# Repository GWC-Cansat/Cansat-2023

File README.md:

# Cansat-2023
The GWC Cansat 2023 files

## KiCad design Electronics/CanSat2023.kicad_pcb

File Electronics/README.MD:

The electronic files for cansat 2023

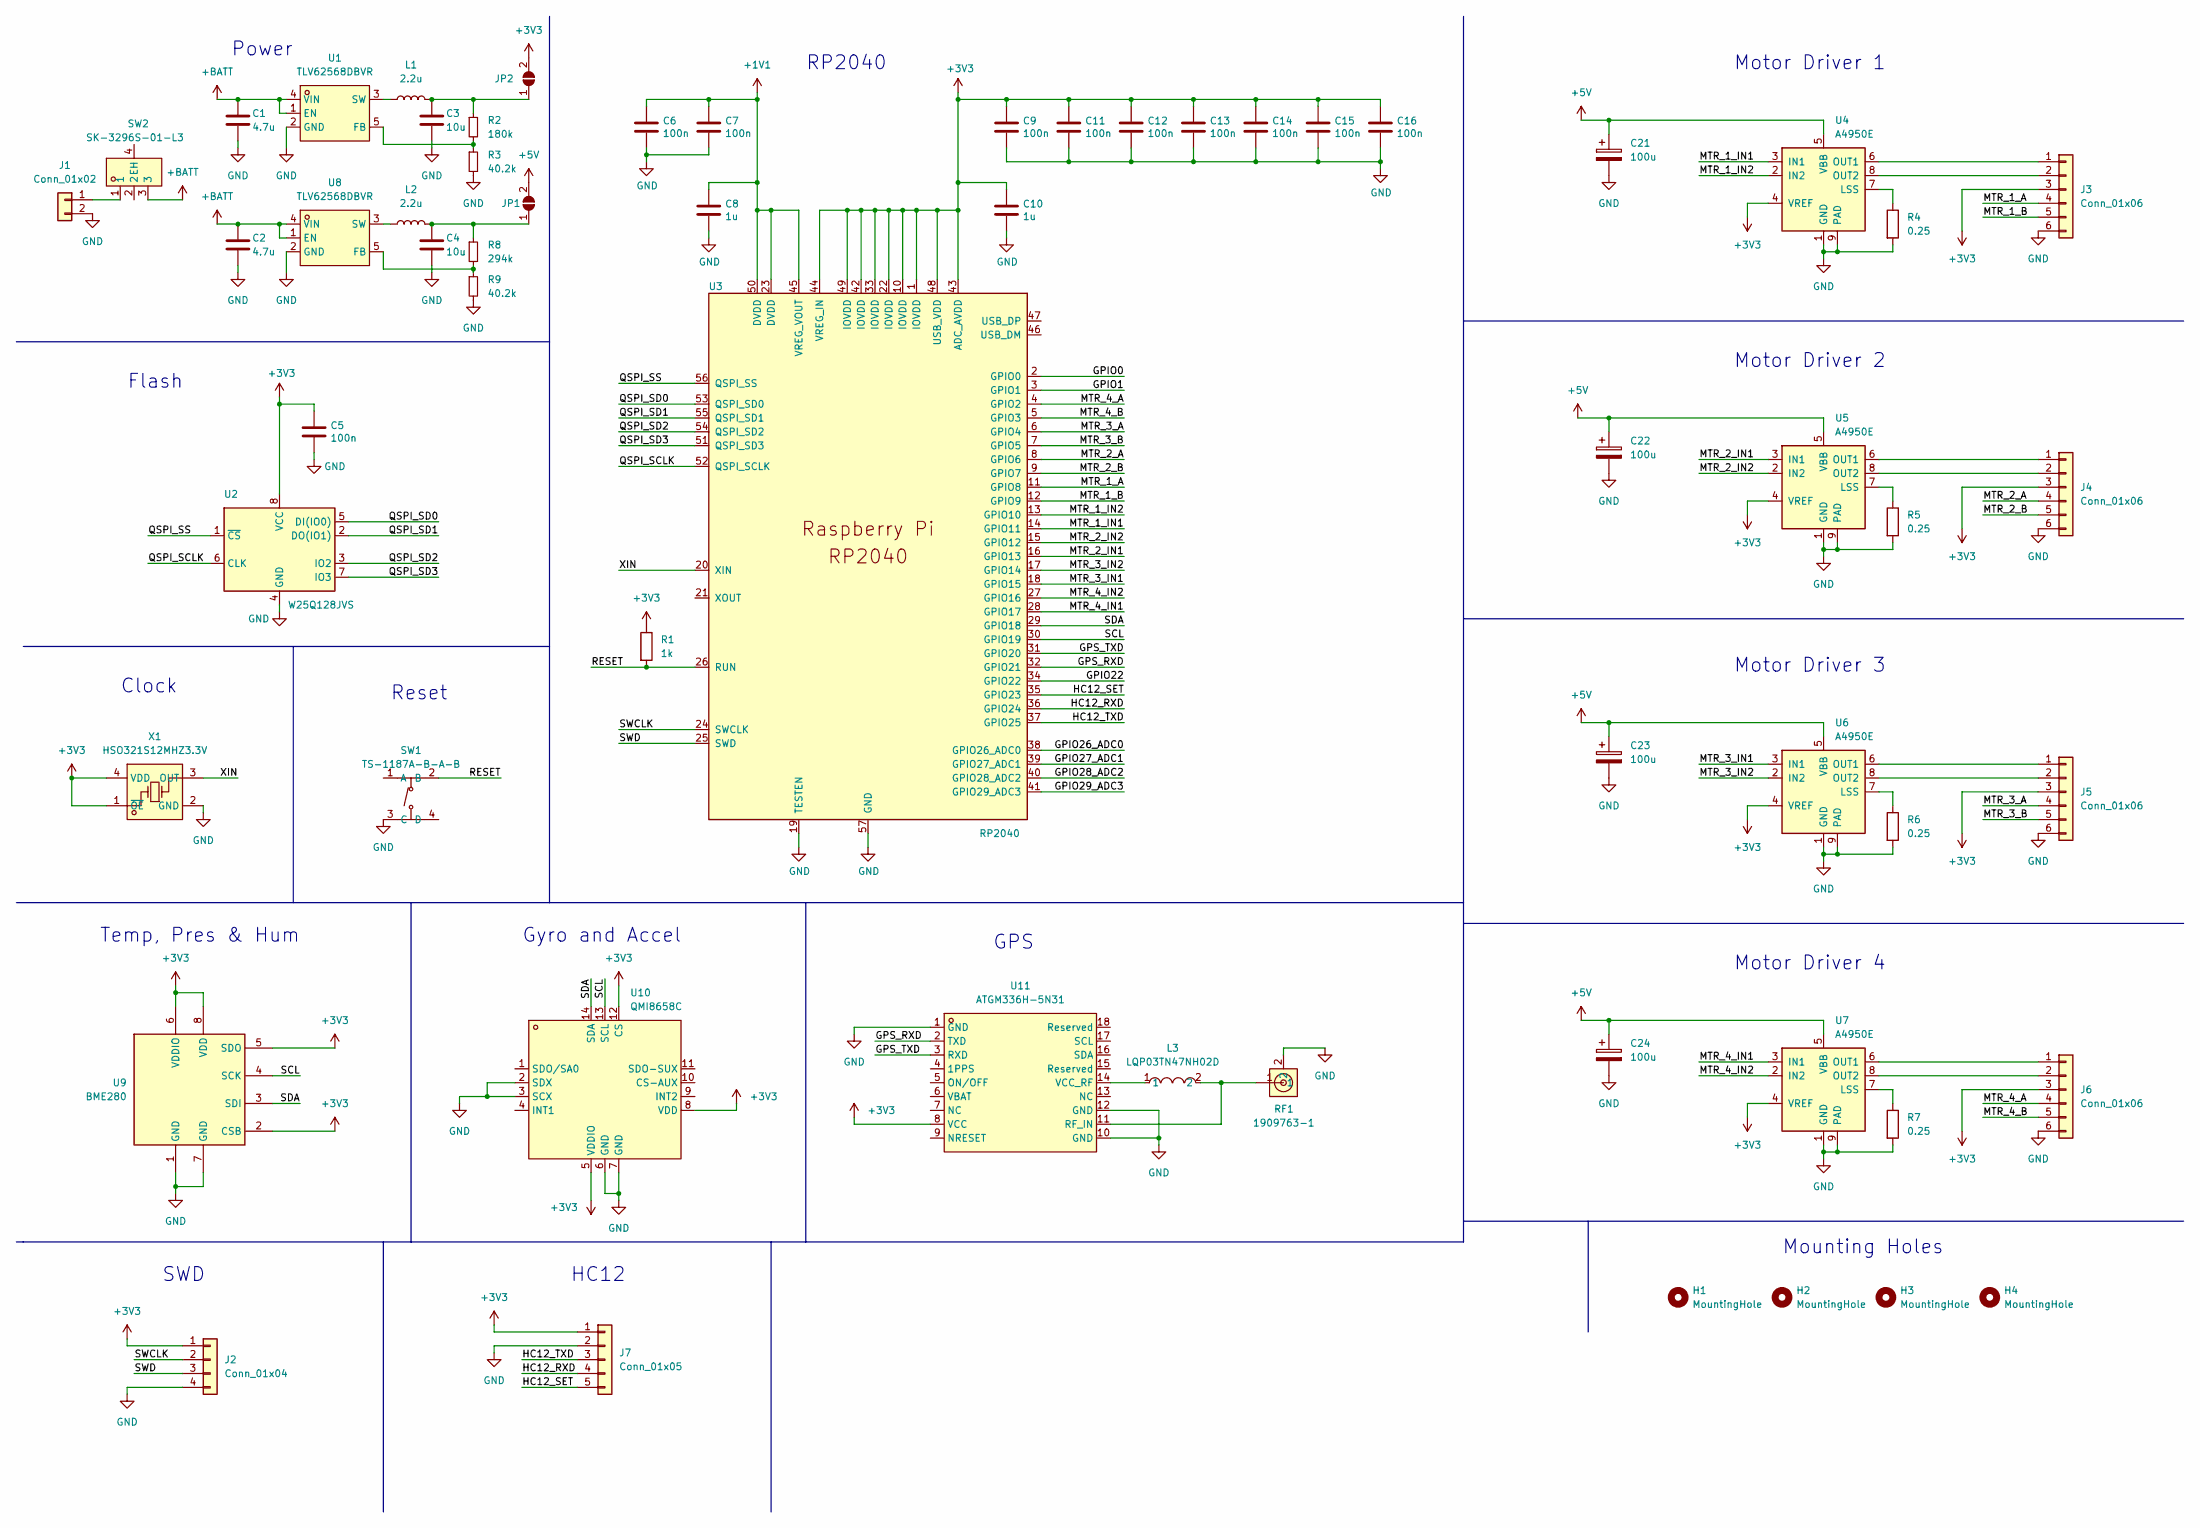
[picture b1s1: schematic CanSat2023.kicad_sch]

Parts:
C1, C2: 4.7u; C_0402_1005Metric; LCSC C368809
C3, C4: 10u; C_0201_0603Metric; LCSC C181043
C5, C6, C7, C9, C11, C12, C13, C14, C15, C16: 100n; C_0402_1005Metric; LCSC C1525
C8, C10: 1u; C_0402_1005Metric; LCSC C14445
C21, C22, C23, C24: 100u; CP_Elec_6.3x5.4; LCSC C97805
H1, H2, H3, H4: MountingHole; MountingHole_4mm
J1: Conn_01x02; JST_PH_B2B-PH-K_1x02_P2.00mm_Vertical
J2: Conn_01x04; PinHeader_1x04_P1.27mm_Vertical
J3, J4, J5, J6: Conn_01x06; JST_SH_SM06B-SRSS-TB_1x06-1MP_P1.00mm_Horizontal; LCSC C160405
J7: Conn_01x05; PinHeader_1x05_P1.27mm_Vertical
JP1, JP2: SolderJumper_2_Open; R_0402_1005Metric
L1, L2: 2.2u; L_0805_2012Metric; LCSC C479898
L3: LQP03TN47NH02D; L0201-RD; LCSC Part C162618
R1: 1k; R_0402_1005Metric; LCSC C106235
R2: 180k; R_0201_0603Metric; LCSC C295779
R3, R9: 40.2k; R_0201_0603Metric; LCSC C166207
R4, R5, R6, R7: 0.25; R_0805_2012Metric; LCSC C158131
R8: 294k; R_0201_0603Metric; LCSC C166254
RF1: 1909763-1; ANT-SMD_1909763-1; LCSC Part C392444
SW1: TS-1187A-B-A-B; SW-SMD_4P-L5.1-W5.1-P3.70-LS6.5-TL-2; LCSC Part C318884
SW2: SK-3296S-01-L3; SW-SMD_SK-3296S-01-L3; LCSC Part C319019
U1, U8: TLV62568DBVR; SOT-23-5_L3.0-W1.7-P0.95-LS2.8-BR; LCSC Part C163219
U2: W25Q128JVS; SOIC-8_5.23x5.23mm_P1.27mm; LCSC C97521
U3: RP2040; RP2040-QFN-56; LCSC C2040
U4, U5, U6, U7: A4950E; SOIC-8-1EP_3.9x4.9mm_P1.27mm_EP2.41x3.3mm; LCSC C82404
U9: BME280; Bosch_LGA-8_2.5x2.5mm_P0.65mm_ClockwisePinNumbering; LCSC C92489
U10: QMI8658C; LGA-14_L3.0-W2.5-P0.50-BR; LCSC Part C2842151
U11: ATGM336H-5N31; GPSM-SMD_ATGM336H-TR; LCSC Part C90770
X1: HSO321S12MHZ3.3V; OSC-SMD_4P-L3.2-W2.5-BL; LCSC Part C160457

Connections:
+1V1: C6.1, C7.1, C8.1, U3.23 (DVDD), U3.45 (VREG_VOUT), U3.50 (DVDD)
+3V3: C5.1, C9.1, C10.1, C11.1, C12.1, C13.1, C14.1, C15.1, C16.1, J2.1, J3.3, J4.3, J5.3, J6.3, J7.1, JP2.2 (B), R1.1, U2.8 (VCC), U3.1 (IOVDD), U3.10 (IOVDD), U3.22 (IOVDD), U3.33 (IOVDD), U3.42 (IOVDD), U3.43 (ADC_AVDD), U3.44 (VREG_IN), U3.48 (USB_VDD), U3.49 (IOVDD), U4.4 (VREF), U5.4 (VREF), U6.4 (VREF), U7.4 (VREF), U9.2 (CSB), U9.5 (SDO), U9.6 (VDDIO), U9.8 (VDD), U10.5 (VDDIO), U10.8 (VDD), U10.12 (CS), U11.8 (VCC), X1.1 (~OE), X1.4 (VDD)
+5V: C21.1, C22.1, C23.1, C24.1, JP1.2 (B), U4.5 (VBB), U5.5 (VBB), U6.5 (VBB), U7.5 (VBB)
+BATT: C1.1, C2.1, SW2.3, U1.1 (EN), U1.4 (VIN), U8.1 (EN), U8.4 (VIN)
/GPIO0: U3.2 (GPIO0)
/GPIO1: U3.3 (GPIO1)
/GPIO22: U3.34 (GPIO22)
/GPIO26_ADC0: U3.38 (GPIO26_ADC0)
/GPIO27_ADC1: U3.39 (GPIO27_ADC1)
/GPIO28_ADC2: U3.40 (GPIO28_ADC2)
/GPIO29_ADC3: U3.41 (GPIO29_ADC3)
/GPS_RXD: U3.32 (GPIO21), U11.2 (TXD)
/GPS_TXD: U3.31 (GPIO20), U11.3 (RXD)
/HC12_RXD: J7.4, U3.36 (GPIO24)
/HC12_SET: J7.5, U3.35 (GPIO23)
/HC12_TXD: J7.3, U3.37 (GPIO25)
/MTR_1_A: J3.4, U3.11 (GPIO8)
/MTR_1_B: J3.5, U3.12 (GPIO9)
/MTR_1_IN1: U3.14 (GPIO11), U4.3 (IN1)
/MTR_1_IN2: U3.13 (GPIO10), U4.2 (IN2)
/MTR_2_A: J4.4, U3.8 (GPIO6)
/MTR_2_B: J4.5, U3.9 (GPIO7)
/MTR_2_IN1: U3.16 (GPIO13), U5.3 (IN1)
/MTR_2_IN2: U3.15 (GPIO12), U5.2 (IN2)
/MTR_3_A: J5.4, U3.6 (GPIO4)
/MTR_3_B: J5.5, U3.7 (GPIO5)
/MTR_3_IN1: U3.18 (GPIO15), U6.3 (IN1)
/MTR_3_IN2: U3.17 (GPIO14), U6.2 (IN2)
/MTR_4_A: J6.4, U3.4 (GPIO2)
/MTR_4_B: J6.5, U3.5 (GPIO3)
/MTR_4_IN1: U3.28 (GPIO17), U7.3 (IN1)
/MTR_4_IN2: U3.27 (GPIO16), U7.2 (IN2)
/QSPI_SCLK: U2.6 (CLK), U3.52 (QSPI_SCLK)
/QSPI_SD0: U2.5 (DI(IO0)), U3.53 (QSPI_SD0)
/QSPI_SD1: U2.2 (DO(IO1)), U3.55 (QSPI_SD1)
/QSPI_SD2: U2.3 (IO2), U3.54 (QSPI_SD2)
/QSPI_SD3: U2.7 (IO3), U3.51 (QSPI_SD3)
/QSPI_SS: U2.1 (~CS), U3.56 (QSPI_SS)
/RESET: R1.2, SW1.2 (B), U3.26 (RUN)
/SCL: U3.30 (GPIO19), U9.4 (SCK), U10.13 (SCL)
/SDA: U3.29 (GPIO18), U9.3 (SDI), U10.14 (SDA)
/SWCLK: J2.2, U3.24 (SWCLK)
/SWD: J2.3, U3.25 (SWD)
/XIN: U3.20 (XIN), X1.3 (OUT)
GND: C1.2, C2.2, C3.2, C4.2, C5.2, C6.2, C7.2, C8.2, C9.2, C10.2, C11.2, C12.2, C13.2, C14.2, C15.2, C16.2, C21.2, C22.2, C23.2, C24.2, J1.2, J2.4, J3.6, J4.6, J5.6, J6.6, J7.2, R3.2, R4.2, R5.2, R6.2, R7.2, R9.2, RF1.2, SW1.3 (C), U1.2 (GND), U2.4 (GND), U3.19 (TESTEN), U3.57 (GND), U4.1 (GND), U4.9 (PAD), U5.1 (GND), U5.9 (PAD), U6.1 (GND), U6.9 (PAD), U7.1 (GND), U7.9 (PAD), U8.2 (GND), U9.1 (GND), U9.7 (GND), U10.2 (SDX), U10.3 (SCX), U10.6 (GND), U10.7 (GND), U11.1 (GND), U11.10 (GND), U11.12 (GND), X1.2 (GND)
unnamed: J1.1, SW2.1
unnamed: J3.1, U4.6 (OUT1)
unnamed: J3.2, U4.8 (OUT2)
unnamed: J4.1, U5.6 (OUT1)
unnamed: J4.2, U5.8 (OUT2)
unnamed: J5.1, U6.6 (OUT1)
unnamed: J5.2, U6.8 (OUT2)
unnamed: J6.1, U7.6 (OUT1)
unnamed: J6.2, U7.8 (OUT2)
unnamed: C4.1, JP1.1 (A), L2.2, R8.1
unnamed: C3.1, JP2.1 (A), L1.2, R2.1
unnamed: R2.2, R3.1, U1.5 (FB)
unnamed: L1.1, U1.3 (SW)
unnamed: R4.1, U4.7 (LSS)
unnamed: R5.1, U5.7 (LSS)
unnamed: R6.1, U6.7 (LSS)
unnamed: R7.1, U7.7 (LSS)
unnamed: R8.2, R9.1, U8.5 (FB)
unnamed: L2.1, U8.3 (SW)
unnamed: L3.2, RF1.1, U11.11 (RF_IN)
unnamed: L3.1, U11.14 (VCC_RF)

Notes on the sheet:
SWD
Gyro and Accel
Motor Driver 3
Motor Driver 2
Mounting Holes
RP2040
HC12
Clock
Motor Driver 4
Motor Driver 1
GPS
Power
Reset
Flash
Temp, Pres & Hum

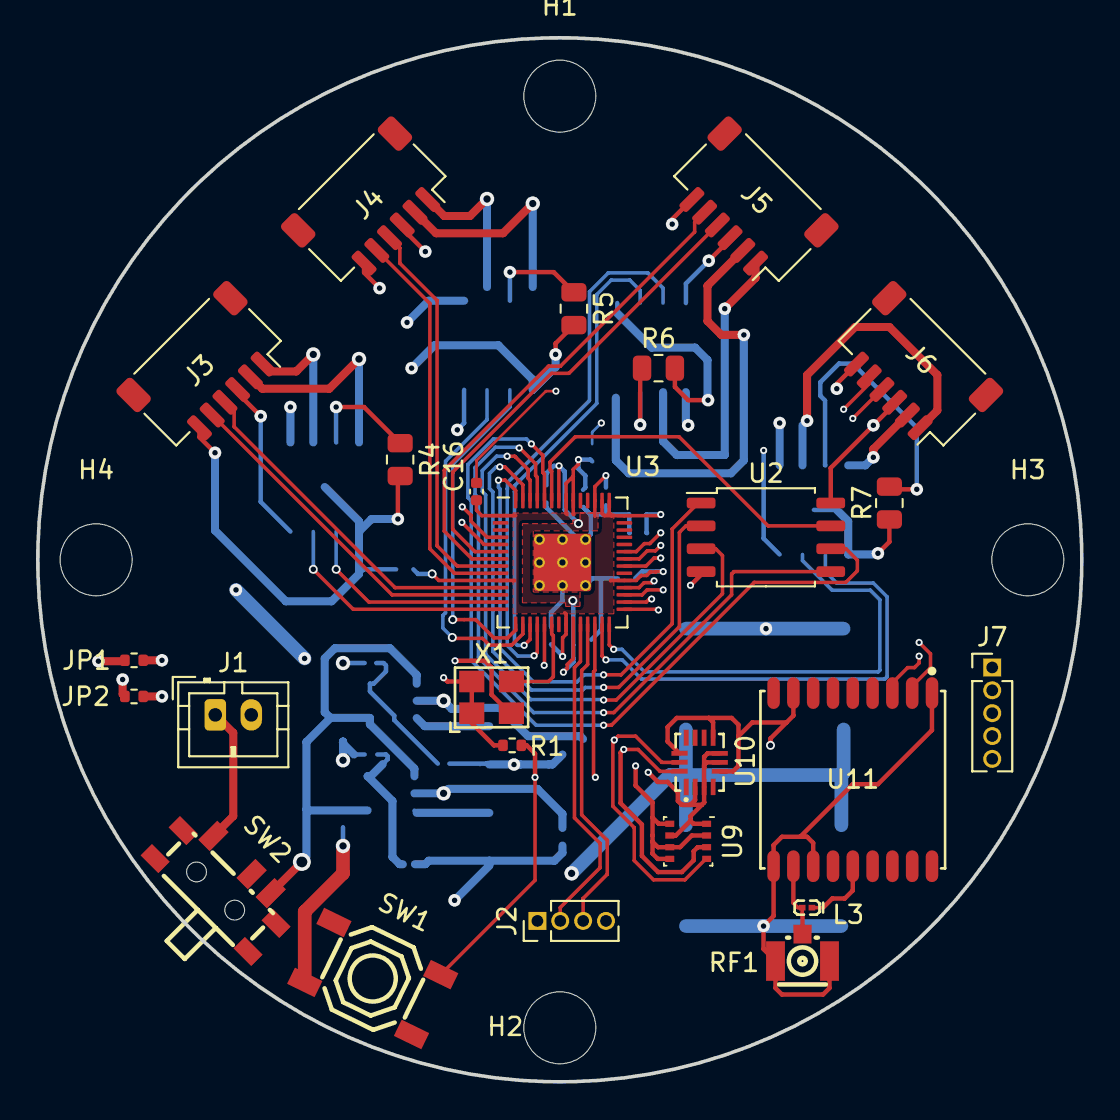
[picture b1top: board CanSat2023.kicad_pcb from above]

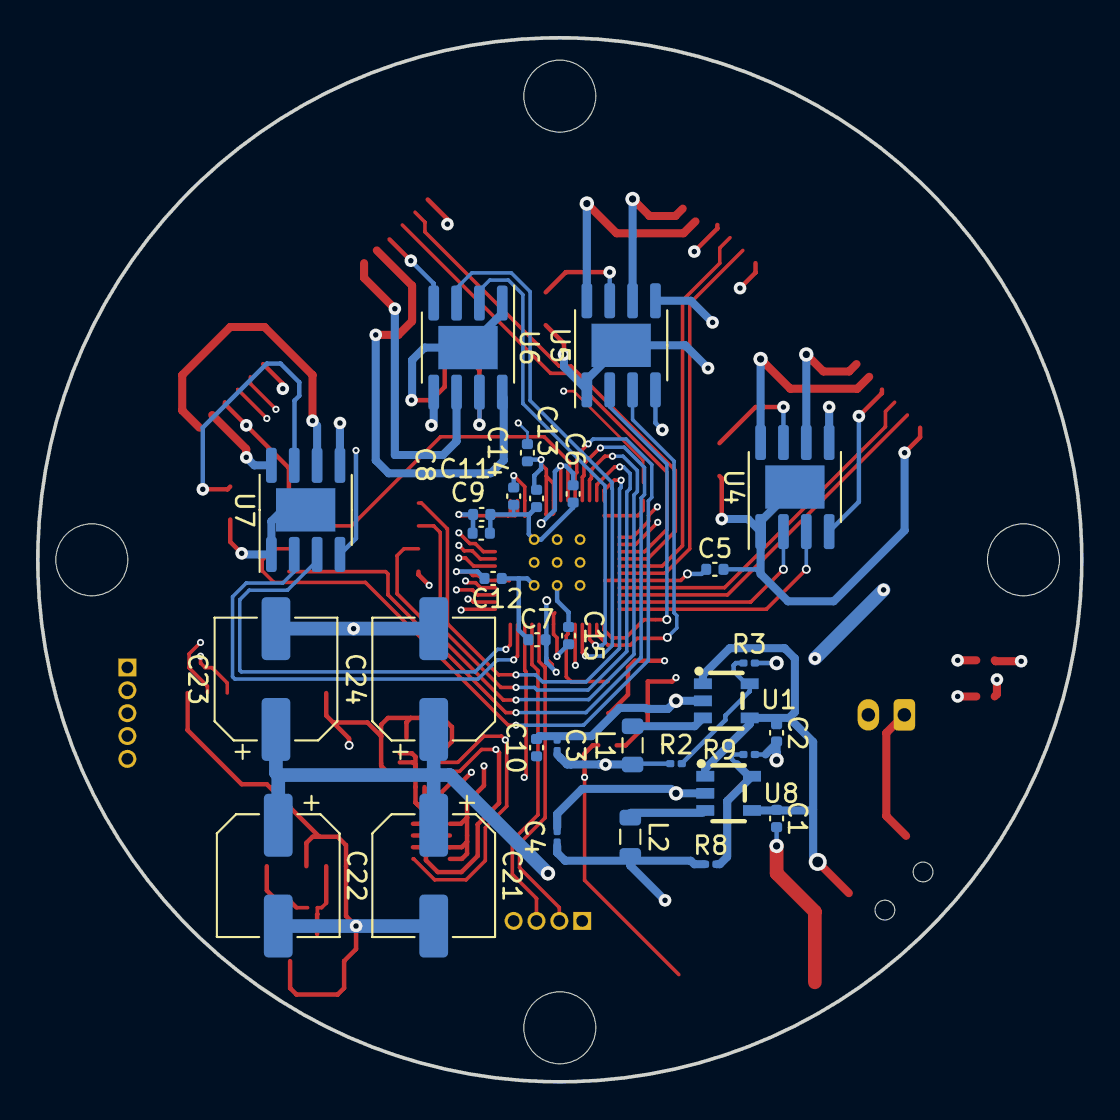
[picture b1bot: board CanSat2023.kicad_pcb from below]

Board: 4 copper layers, 58.0 x 58.0 mm, 60 parts (31 on the bottom side), 59 nets.

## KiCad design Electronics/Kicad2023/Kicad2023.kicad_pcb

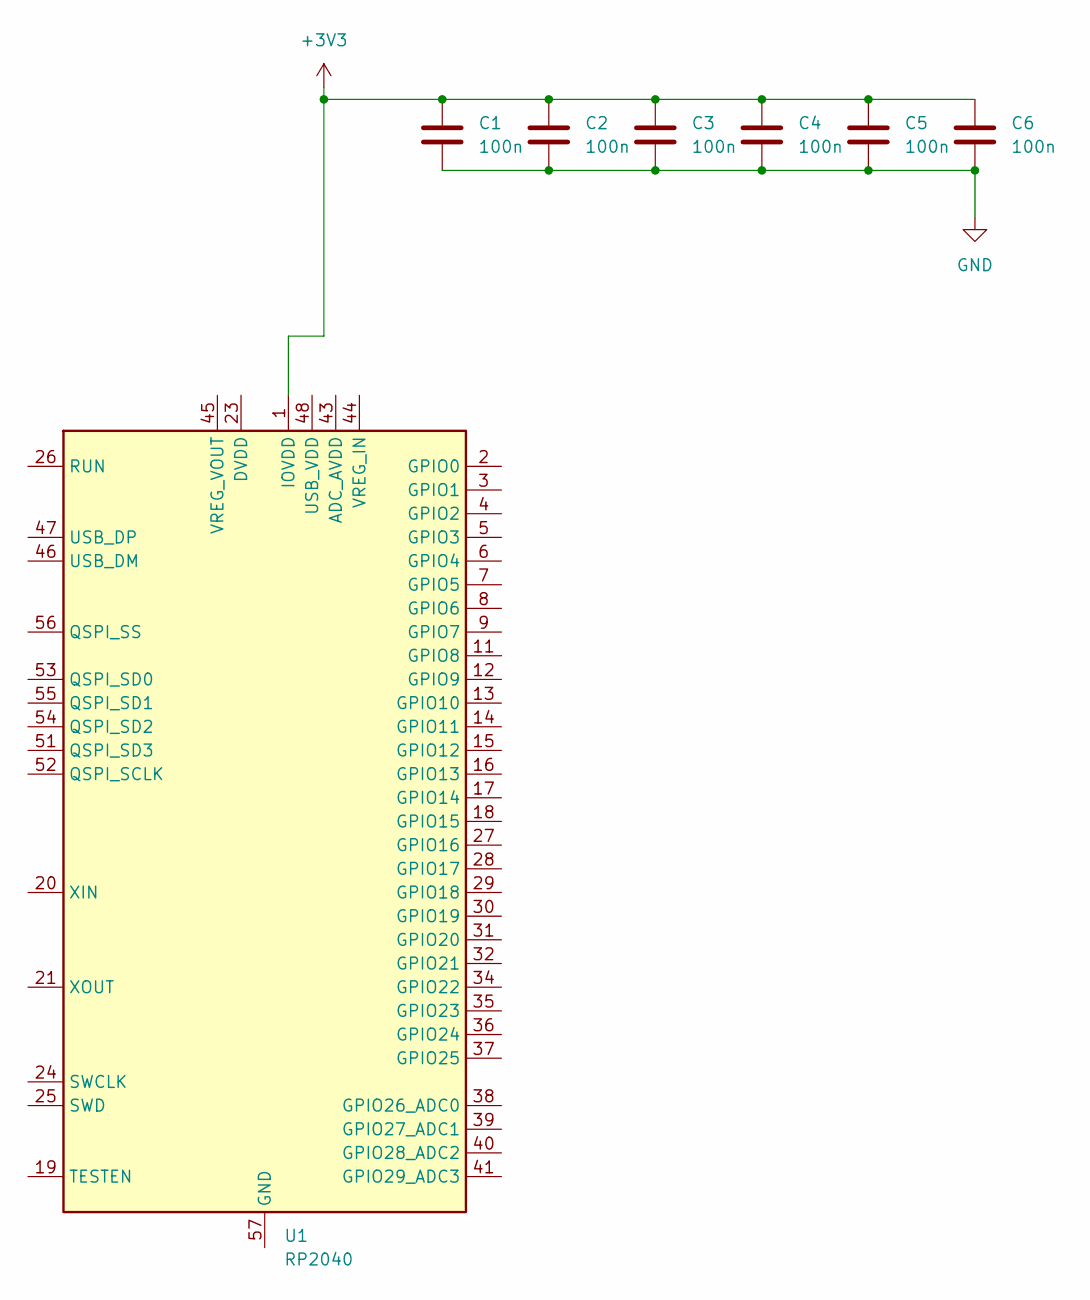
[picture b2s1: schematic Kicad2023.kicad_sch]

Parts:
C1, C2, C3, C4, C5, C6: 100n; C_0201_0603Metric
U1: RP2040; QFN-56-1EP_7x7mm_P0.4mm_EP3.2x3.2mm

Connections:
+3V3: C1.1, C2.1, C3.1, C4.1, C5.1, C6.1, U1.1 (IOVDD), U1.10 (IOVDD), U1.22 (IOVDD), U1.33 (IOVDD), U1.42 (IOVDD), U1.49 (IOVDD)
GND: C1.2, C2.2, C3.2, C4.2, C5.2, C6.2
unnamed: U1.23 (DVDD), U1.50 (DVDD)

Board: 2 copper layers, 7 parts (0 on the bottom side), 3 nets, no tracks yet.

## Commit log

2022-10-04 Started schematic design
2022-11-07 Added files
2022-11-08 Correct files
2023-03-07 Adding files
